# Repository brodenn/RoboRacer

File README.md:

# RoboRacer

## 📄 [Download the full report: Report ghost divsion.pdf](./Report%20ghost%20divsion.pdf)

Welcome to the RoboRacer project! This repository contains the full stack for the Omnix robot platform, including embedded firmware, Python-based visualization and configuration tools, and supporting documentation.

---

## Project Images

### Robots

---

# Omnix Overview

The `omnix` robot is a core vehicle in the RoboRacer project, equipped with omni wheels for enhanced maneuverability. It handles sensor management, motor control, AI steering, and wireless communication, and is supported by a Python toolkit for visualization and configuration.

---

## Directory Structure

- **`ai.cpp` / `ai.h`**: AI steering logic for autonomous navigation.
- **`controller.cpp` / `controller.h`**: Gamepad/controller input management.
- **`globals.cpp` / `globals.h`**: Global variables and constants.
- **`imu.cpp` / `imu.h`**: IMU (Inertial Measurement Unit) initialization and data reading.
- **`interrupts.cpp` / `interrupts.h`**: Sensor interrupt configuration and management.
- **`motors.cpp` / `motors.h`**: Motor initialization and control.
- **`mux.cpp` / `mux.h`**: I2C multiplexer for sensor communication.
- **`params.cpp` / `params.h`**: Steering and sensor parameter management.
- **`sensors.cpp` / `sensors.h`**: Sensor initialization, reading, and management.
- **`tasks.cpp` / `tasks.h`**: FreeRTOS tasks for sensors, motors, and logic.
- **`udp_handler.cpp` / `udp_comm.h`**: UDP communication for parameters and telemetry.
- **`udp_sender.cpp`**: Telemetry data transmission over UDP.
- **`wifi_setup.cpp` / `wifi_setup.h`**: WiFi and UDP setup.
- **`xshut.cpp` / `xshut.h`**: Sensor power control via GPIO.
- **`omnix_py/`**: Python scripts for visualization, configuration, and debugging.

---

## Python Toolkit Overview

The `omnix_py` directory provides Python scripts that complement the robot's firmware:

- **`main.py`**: Entry point for the Python tools (UI and visualizer).
- **`udp_comm.py`**: UDP communication for telemetry and commands.
- **`ui.py`**: Tkinter-based GUI for parameter tuning and monitoring.
- **`visualizer.py`**: Pygame-based visualization of sensor and IMU data.
- **`config.py`**: Shared configuration (ports, IPs, parameters).
- **`logger.py`**: Telemetry and sensor data logging to CSV.

---

## Key Features

- **Omni Wheels**: Smooth, precise movement in any direction.
- **Sensor Management**: Multiple VL53L4CD sensors via I2C multiplexers.
- **Motor Control**: Smooth updates and autonomous driving logic.
- **AI Steering**: Wall centering, curve anticipation, and obstacle avoidance.
- **Wireless Communication**: Real-time telemetry and parameter updates via UDP.
- **IMU Integration**: Acceleration, gyroscope, and temperature data.
- **Python Tools**: UI for parameter tuning and real-time telemetry visualization.

---

## Setup Instructions

1. Initialize the I2C buses and configure the multiplexer.
2. Set up sensors, motors, and WiFi.
3. Start FreeRTOS tasks for sensor reading, motor control, and auxiliary logic.
4. Run the Python tools using `python3 main.py` in the `omnix_py` directory.

---

## Usage

- **Autonomous Mode**: AI steering logic controls the motors based on sensor data.
- **Controller Mode**: Use a gamepad for manual control.
- **Python Tools**: Tune parameters and monitor telemetry in real time.

---

## Dependencies

- [ArduinoJson](https://arduinojson.org/)
- [Adafruit Motor Shield Library](https://github.com/adafruit/Adafruit_Motor_Shield_V2_Library)
- [Adafruit LSM6DSOX Library](https://github.com/adafruit/Adafruit_LSM6DSOX)
- [Bluepad32](https://github.com/ricardoquesada/Bluepad32)
- [VL53L4CD Library](https://github.com/stm32duino/VL53L4CD)
- **Python**: Requires Python 3.8+ with the following libraries:
  - `pygame`
  - `tkinter`
  - `socket`
  - `json`
  - `csv`

---

## Visualizer Example

---

## Configuration GUI

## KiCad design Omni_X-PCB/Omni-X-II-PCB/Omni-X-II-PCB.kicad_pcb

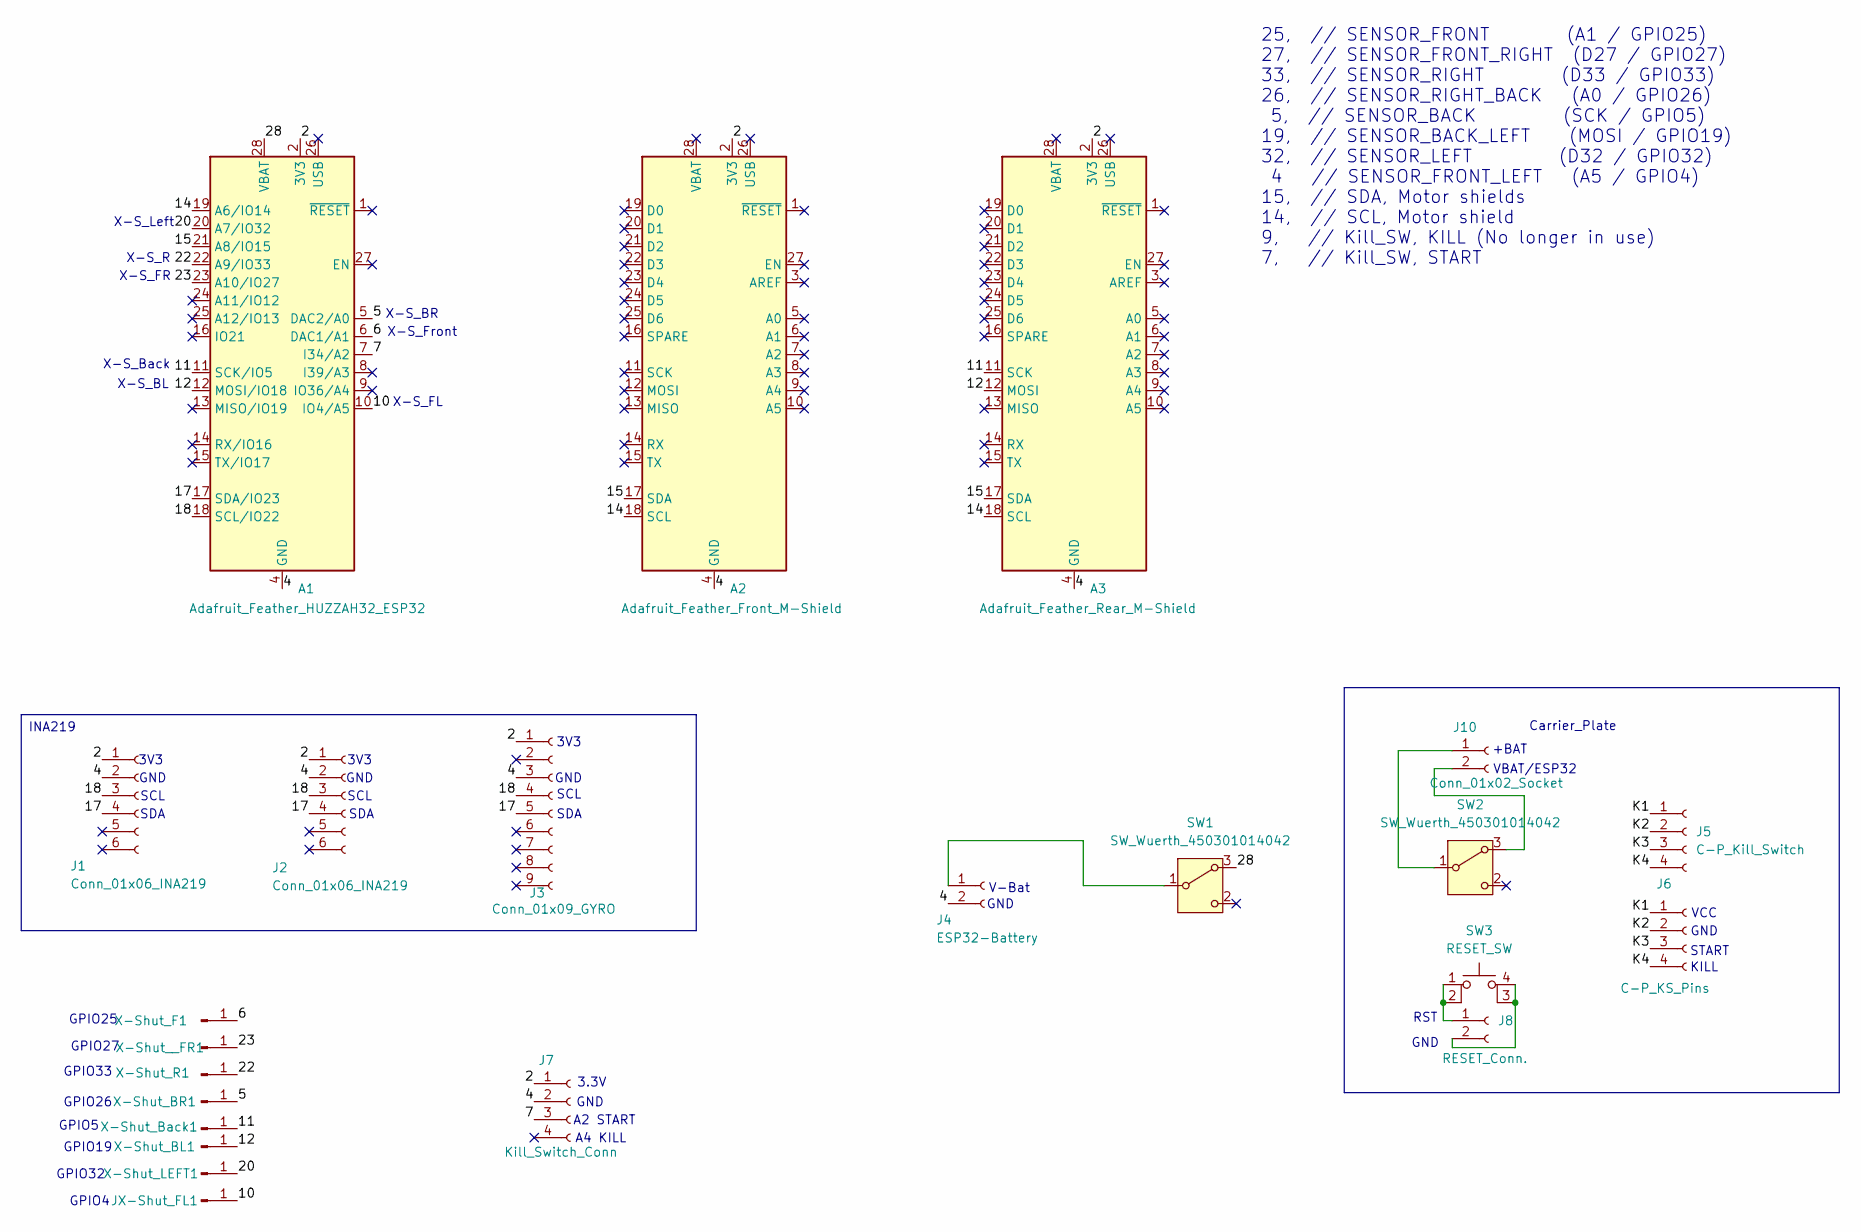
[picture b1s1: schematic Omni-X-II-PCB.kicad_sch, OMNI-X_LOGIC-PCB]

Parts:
A1: Adafruit_Feather_HUZZAH32_ESP32; Adafruit_Feather
A2: Adafruit_Feather_Front_M-Shield; Adafruit_Feather
A3: Adafruit_Feather_Rear_M-Shield; Adafruit_Feather
J1, J2: Conn_01x06_INA219; PinSocket_1x06_P2.54mm_Vertical
J3: Conn_01x09_GYRO; PinSocket_1x09_P2.54mm_Vertical
J4: ESP32-Battery; JST_EH_B2B-EH-A_1x02_P2.50mm_Vertical
J5: C-P_Kill_Switch; PinHeader_1x04_P2.54mm_Vertical
J6: C-P_KS_Pins; PinHeader_1x04_P2.54mm_Vertical
J7: Kill_Switch_Conn; PinHeader_1x04_P2.54mm_Vertical
J8: RESET_Conn.; PinHeader_1x02_P2.54mm_Vertical
J10: Conn_01x02_Socket; PinHeader_1x02_P2.54mm_Vertical
JX-Shut_FL1: Conn_01x01_Pin; PinHeader_1x01_P2.54mm_Vertical
SW1, SW2: SW_Wuerth_450301014042; SW_Slide-03_Wuerth-WS-SLTV_10x2.5x6.4_P2.54mm
SW3: RESET_SW; Tac_Switch_THT
X-Shut_BL1: Conn_01x01_Pin; PinHeader_1x01_P2.54mm_Vertical
X-Shut_BR1: Conn_01x01_Pin; PinHeader_1x01_P2.54mm_Vertical
X-Shut_Back1: Conn_01x01_Pin; PinHeader_1x01_P2.54mm_Vertical
X-Shut_F1: Conn_01x01_Pin; PinHeader_1x01_P2.54mm_Vertical
X-Shut_LEFT1: Conn_01x01_Pin; PinHeader_1x01_P2.54mm_Vertical
X-Shut_R1: Conn_01x01_Pin; PinHeader_1x01_P2.54mm_Vertical
X-Shut__FR1: Conn_01x01_Pin; PinHeader_1x01_P2.54mm_Vertical

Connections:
/2: A1.2 (3V3), A2.2 (3V3), A3.2 (3V3), J1.1, J2.1, J3.1, J7.1
/4: A1.4 (GND), A2.4 (GND), A3.4 (GND), J1.2, J2.2, J3.3, J4.2, J7.2
/5: A1.5 (DAC2/A0), X-Shut_BR1.1
/6: A1.6 (DAC1/A1), X-Shut_F1.1
/7: A1.7 (I34/A2), J7.3
/10: A1.10 (IO4/A5), JX-Shut_FL1.1
/11: A1.11 (SCK/IO5), A3.11 (SCK), X-Shut_Back1.1
/12: A1.12 (MOSI/IO18), A3.12 (MOSI), X-Shut_BL1.1
/14: A1.19 (A6/IO14), A2.18 (SCL), A3.18 (SCL)
/15: A1.21 (A8/IO15), A2.17 (SDA), A3.17 (SDA)
/17: A1.17 (SDA/IO23), J1.4, J2.4, J3.5
/18: A1.18 (SCL/IO22), J1.3, J2.3, J3.4
/20: A1.20 (A7/IO32), X-Shut_LEFT1.1
/22: A1.22 (A9/IO33), X-Shut_R1.1
/23: A1.23 (A10/IO27), X-Shut__FR1.1
/28: A1.28 (VBAT), SW1.3 (A)
/K1: J5.1, J6.1
/K2: J5.2, J6.2
/K3: J5.3, J6.3
/K4: J5.4, J6.4
unnamed: J4.1, SW1.1 (B)
unnamed: J8.1, SW3.1, SW3.2
unnamed: J8.2, SW3.3 (K), SW3.4 (A)
unnamed: J10.1, SW2.1 (B)
unnamed: J10.2, SW2.3 (A)

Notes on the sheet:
GPIO33
KILL
X-S_Front
X-S_R
X-S_BL
X-S_BR
RST
START
A2 START
X-S_FL
GPIO19
GND
SCL
GPIO4
A4 KILL
25, // SENSOR_FRONT (A1 / GPIO25) 27, // SENSOR_FRONT_RIGHT (D27 / GPIO27) 33, // SENSOR_RIGHT (D33 / GPIO33) 26, // SENSOR_RIGHT_BACK (A0 / GPIO26) 5, // SENSOR_BACK (SCK / GPIO5) 19, // SENSOR_BACK_LEFT (MOSI / GPIO19) 32, // SENSOR_LEFT (D32 / GPIO32) 4 // SENSOR_FRONT_LEFT (A5 / GPIO4) 15, // S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
VCC
GPIO26
SDA
VBAT/ESP32
3V3
GPIO32
V-Bat
X-S_FR
X-S_Left
X-S_Back
GPIO27
Carrier_Plate
+BAT
GPIO25
3.3V
GPIO5
INA219

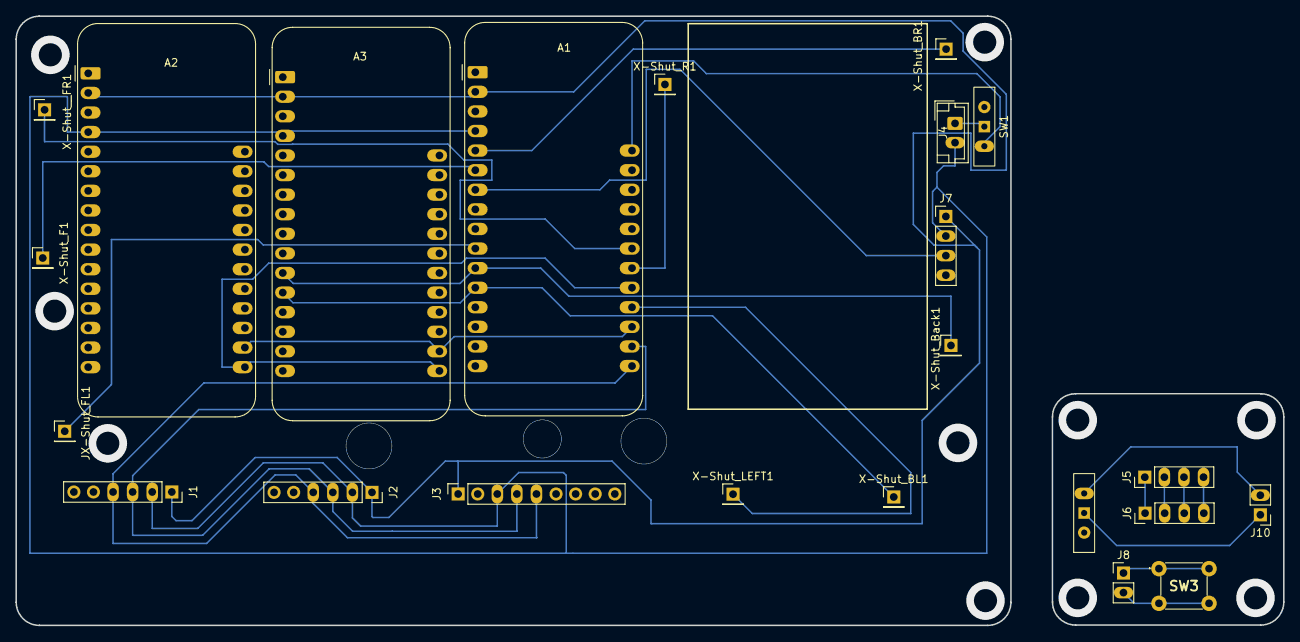
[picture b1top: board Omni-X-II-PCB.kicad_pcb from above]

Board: 2 copper layers, 164.4 x 79.0 mm, 23 parts (0 on the bottom side), 25 nets.

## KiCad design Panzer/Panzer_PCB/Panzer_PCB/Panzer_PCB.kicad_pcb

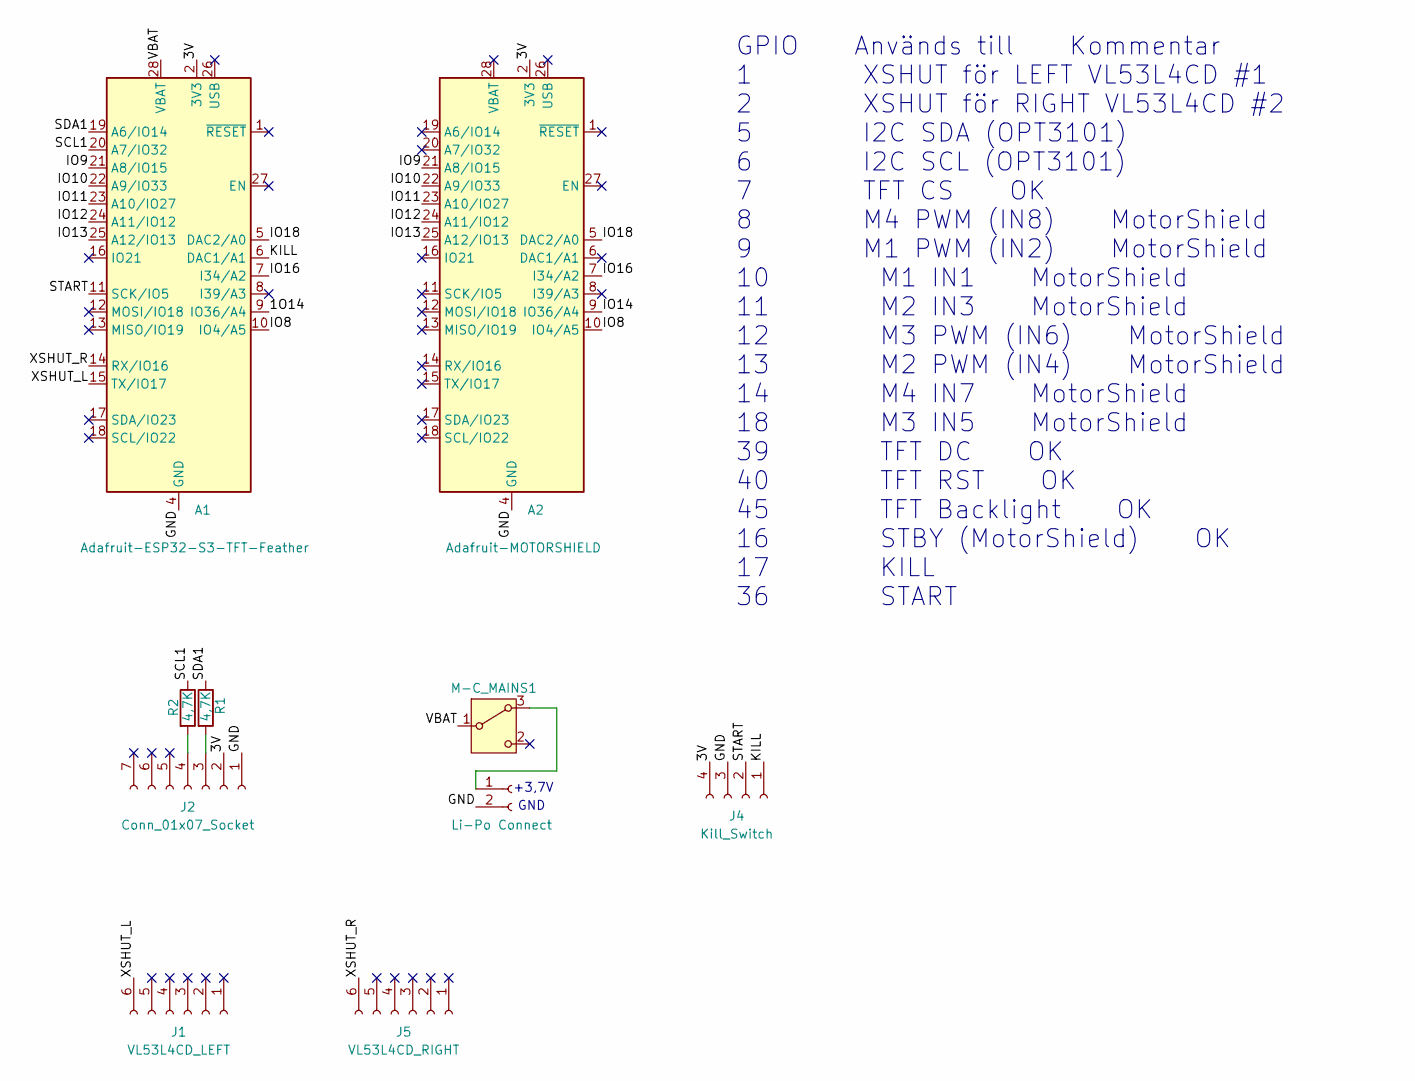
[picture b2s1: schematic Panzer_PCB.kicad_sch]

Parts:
A1: Adafruit-ESP32-S3-TFT-Feather; Adafruit_Feather_WithMountingHoles
A2: Adafruit-MOTORSHIELD; Adafruit_Feather_WithMountingHoles
J1: VL53L4CD_LEFT; PinHeader_1x06_P2.54mm_Vertical
J2: Conn_01x07_Socket; PinSocket_1x07_P2.54mm_Vertical
J3: Li-Po Connect; PinHeader_1x02_P2.54mm_Vertical
J4: Kill_Switch; PinHeader_1x04_P2.54mm_Vertical
J5: VL53L4CD_RIGHT; PinHeader_1x06_P2.54mm_Vertical
M-C_MAINS1: SW_Wuerth_450301014042; SW_Slide-03_Wuerth-WS-SLTV_10x2.5x6.4_P2.54mm
R1, R2: 4,7K; R_Axial_DIN0414_L11.9mm_D4.5mm_P15.24mm_Horizontal

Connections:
/1O14: A1.9 (IO36/A4)
/3V: A1.2 (3V3), A2.2 (3V3), J2.2, J4.4
/GND: A1.4 (GND), A2.4 (GND), J2.1, J3.2, J4.3
/IO8: A1.10 (IO4/A5), A2.10 (IO4/A5)
/IO9: A1.21 (A8/IO15), A2.21 (A8/IO15)
/IO10: A1.22 (A9/IO33), A2.22 (A9/IO33)
/IO11: A1.23 (A10/IO27), A2.23 (A10/IO27)
/IO12: A1.24 (A11/IO12), A2.24 (A11/IO12)
/IO13: A1.25 (A12/IO13), A2.25 (A12/IO13)
/IO14: A2.9 (IO36/A4)
/IO16: A1.7 (I34/A2), A2.7 (I34/A2)
/IO18: A1.5 (DAC2/A0), A2.5 (DAC2/A0)
/KILL: A1.6 (DAC1/A1), J4.1
/SCL1: A1.20 (A7/IO32), R2.1
/SDA1: A1.19 (A6/IO14), R1.1
/START: A1.11 (SCK/IO5), J4.2
/VBAT: A1.28 (VBAT), M-C_MAINS1.1 (B); also elsewhere on the board
/XSHUT_L: A1.15 (TX/IO17), J1.6
/XSHUT_R: A1.14 (RX/IO16), J5.6
unnamed: J2.3, R1.2
unnamed: J2.4, R2.2
unnamed 21: J3.1, M-C_MAINS1.3 (A); also elsewhere on the board

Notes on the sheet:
+3,7V
GND
GPIO Används till Kommentar 1 XSHUT för LEFT VL53L4CD #1 2 XSHUT för RIGHT VL53L4CD #2 5 I2C SDA (OPT3101) 6 I2C SCL (OPT3101) 7 TFT CS OK 8 M4 PWM (IN8) MotorShield 9 M1 PWM (IN2) MotorShield 10 M1 IN1 MotorShield 11 M2 IN3 MotorShield 12 M3 PWM (IN6) MotorShield 13 M2 PWM (IN4) MotorShield 14 M4 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

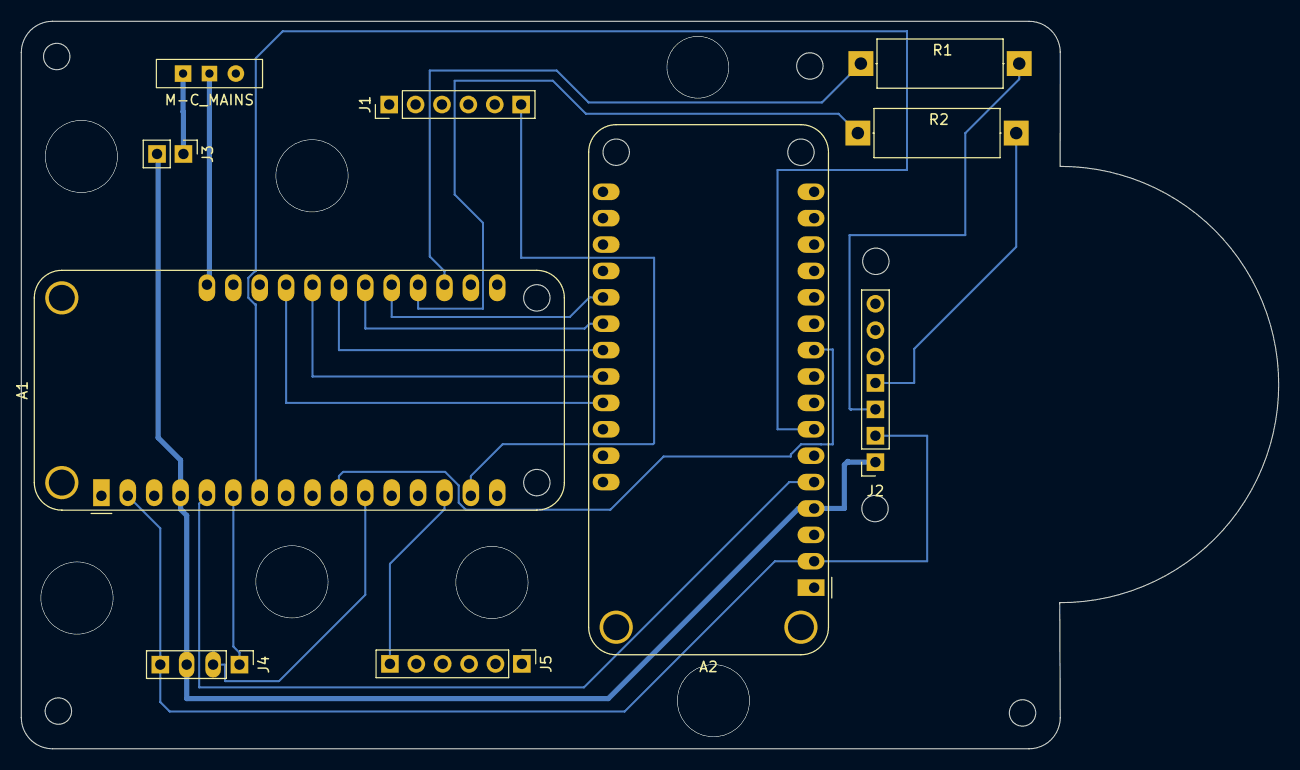
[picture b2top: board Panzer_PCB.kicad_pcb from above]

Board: 2 copper layers, 121.0 x 70.0 mm, 10 parts (0 on the bottom side), 20 nets.

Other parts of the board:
M-C_MAINS: SW_Wuerth_450301014042; SW_Slide-03_Wuerth-WS-SLTV_10x2.5x6.4_P2.54mm

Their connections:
/VBAT: M-C_MAINS.1 (B); also elsewhere on the board
unnamed 21: M-C_MAINS.3 (A); also elsewhere on the board

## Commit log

2025-02-03 Initial project structure setup
2025-02-05 Added RnD folder
2025-04-24 Add omnix
2025-04-25 Panzer Files
2025-04-30 Add detailed documentation for the Omnix robot and remove empty README files for vehicle1_roverc and vehicle3_tank
2025-05-04 Update README.md to add VL53L4CD Library reference and remove License section
2025-05-04 Remove empty README.md file from common directory
2025-05-05 Refactor sensor mapping and update thresholds in mux.cpp and sensors.cpp
    - Updated sensor order in mux.cpp for improved clarity and consistency.
    - Adjusted threshold selection logic in sensors.cpp to ensure correct thresholds are applied based on sensor positions.
    - Enhanced fallback logic for unreliable sensor data in sensors.cpp.
    - Cleaned up comments for better understanding of the code flow.
    Optimize task priorities in omnix.ino
    - Changed the priority of the sensor task from 3 to 1 to improve system responsiveness.
2025-05-05 Add Python tools section to README.md with script descriptions and usage instructions
2025-05-05 Refactor and restructure project: removed visualizer.py, added config, logger, main, udp_comm, and ui modules
    - Deleted visualizer.py and integrated its functionality into a new structure.
    - Created config.py for centralized configuration management.
    - Implemented logger.py for logging functionality with CSV output.
    - Developed main.py to initialize and run the application with threading for UI and UDP communication.
    - Added udp_comm.py for handling UDP communication with the ESP32.
    - Introduced ui.py for a Tkinter-based user interface to control robot parameters and settings.
2025-05-05 Update README.md to specify Python 3 for running main.py in omnix_py directory
2025-05-05 Updated panzer code
    Added OTA and webserver, Obstacle handling (rudimentary), sensor data retrieval logic.
2025-05-06 Omni_x-PCB
    PCB-files for Omnix-X
2025-05-08 Panzer_ODT
    New Panzer Ccode
2025-05-09 Refactor code structure for improved readability and maintainability
2025-05-11 updated steering algorithm
2025-05-11 updated Panzer ODT logic
2025-05-11 improved steering logic
2025-05-13 3 laps in slow mode
2025-05-14 Updates for Panzer
2025-05-14 added Intelligent reverse
2025-05-15 2025-05-15
2025-05-15 added steering algorythm using VL, non functional
2025-05-20 added misc pics
2025-05-28 Implement code changes to enhance functionality and improve performance
2025-05-28 Update README to enhance report visibility
2025-06-06 Reorganize README to improve image section layout and visibility
2025-07-04 Updated panzer component folder
2025-07-04 Some code updates to Panzer# Please enter the commit message for your changes. Lines starting
